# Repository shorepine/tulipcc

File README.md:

# Tulip Creative Computer and AMYboard - portable programmable devices for music, graphics, code and writing

Welcome to the Tulip Creative Computer (Tulip CC) and AMYboard!
 
Tulip is a low power and affordable self-contained portable computer, with a touchscreen display and sound. It's fully programmable - you write code to define your music, games or anything else you can think of. It boots instantaneously into a Python prompt with a lot of built in support for music synthesis, fast graphics and text, hardware MIDI, network access and external sensors. Dive right into making something without distractions or complications. 

The entire system is dedicated to your code, the display and sound, running in real time, on specialized hardware. The hardware and software are fully open source and anyone can [buy one](https://tulip.computer/) or [build one](docs/tulip_build.md). You can use Tulip to make music, code, art, games, or just write. 

[AMYboard](https://amyboard.com) is a headless (no screen) version of Tulip with more audio capability - audio input, modular 10hp and 10vpp audio, S/PDIF digital audio, CV jacks, SD card. It's based on the Tulip code but focused on music synthesis. 

You can now even [run Tulip on the web](https://tulip.computer/run) and [AMYboard on the web](https://amyboard.com/editor) and share your creations with anyone!

Tulip and AMYboard are powered by [MicroPython](https://micropython.org), [AMY](https://github.com/shorepine/amy), and [LVGL](https://lvgl.io). The Tulip hardware runs on the ESP32-S3 chip using the [ESP-IDF](https://github.com/espressif/esp-idf).

 * [**Get a Tulip** from our friends at Makerfabs for only US$59](https://tulip.computer)
 * [**Get an AMYboard** from our friends at Makerfabs for only $29.90](https://amyboard.com)
 * [Just got a Tulip CC? **Check out our getting started guide!**](docs/getting_started.md)
 * [Just got an AMYboard? **Check out our getting started guide!**](docs/amyboard/README.md)
 * [Want to make music with your Tulip? **See our music tutorial**](docs/music.md)
 * [See the full **Tulip API**](docs/tulip_api.md)
 * [**Try out Tulip on the web!**](https://tulip.computer/run/)

 [ **Chat about Tulip on our Discord!**](https://discord.gg/TzBFkUb8pG)

**Check out this video!**

[![Tulip, a musical computer based on Micropython
](https://i.ytimg.com/vi/1lYFjQp7Xrw/maxresdefault.jpg)](https://www.youtube.com/watch?v=1lYFjQp7Xrw "Tulip, a musical computer based on Micropython")

You can use Tulip one of three ways:
 * Tulip is available both as an [off the shelf or DIY hardware project (Tulip CC)](https://tulip.computer/)
 * [Tulip runs on the web](https://tulip.computer/run) with (almost) all the same features. 
 * Tulip can also run as a native app for Mac or Linux (or WSL in Windows) as [Tulip Desktop](docs/tulip_desktop.md)

If you're nervous about getting or building the hardware, [try it out on the web!](https://tulip.computer/run)

The hardware Tulip CC supports:

- 8.5MB of RAM - 2MB is available to MicroPython, and 1.5MB is available for OS memory. The rest is used for the graphics framebuffers (which you can use as storage) and the firmware cache. 
- 32MB flash storage, as a filesystem accesible in Python (24MB left over after OS in ROM)
- An [AMY](https://github.com/shorepine/amy) stereo 120-voice synthesizer engine running locally, or as a wireless controller for an [Alles](https://github.com/shorepine/alles) mesh. Tulip's synth supports additive and subtractive oscillators, an excellent FM synthesis engine, samplers, karplus-strong, high quality analog style filters, a sequencer, and much more. We ship Tulip with a drum machine, voices / patch app, and Juno-6 editor.
- Text frame buffer layer, 128 x 50, with ANSI support for 256 colors, inverse, bold, underline, background color
- Up to 32 sprites on screen, drawn per scanline, with collision detection, from a total of 32KB of bitmap memory (1 byte per pixel)
- A 1024 (+128 overscan) by 600 (+100 overscan) background frame buffer to draw arbitrary bitmaps to, or use as RAM, and which can scroll horizontally / vertically
- WiFi, access http via Python requests or TCP / UDP sockets 
- Adjustable display clock and resolution, defaults to 30 FPS at 1024x600.
- 256 colors
- Can load PNGs from disk to set sprites or background, or generate bitmap data from code
- Built in code and text editor
- Built in BBS chat room and file transfer area called **TULIP ~ WORLD**
- USB keyboard, MIDI and mouse support, including hubs 
- Capactive multi-touch support (mouse on Tulip Desktop and Tulip Web)
- MIDI input and output
- I2C / Grove / Mabee connector, compatible with [many I2C devices like joysticks, keyboard, GPIO, DACs, ADCs, hubs](docs/tulip_api.md#i2c--grove--mabee)
- 575mA power usage @ 5V including display, at medium display brightness, can last for hours on LiPo, 18650s, or USB battery pack 

I've been working on Tulip on and off for years over many hardware iterations and hope that someone out there finds it as fun as I have, either making things with Tulip or working on Tulip itself. I'd love feedback, your own Tulip experiments or pull requests to improve the system.

 * [**Any issues with your Tulip CC? Here's our troubleshooting guide**](docs/troubleshooting.md)
 * [**Learn about our roadmap and find out what we're working on next**](https://github.com/orgs/shorepine/projects/1)
 * [**Build your own Tulip**](docs/tulip_build.md)
 * **[You can read more about the "why" or "how" of Tulip on my website!](https://notes.variogram.com/2024/07/30/tulip-available/)** 

## T-Deck Tulip CC

A **new** small option: get yourself a [T-Deck](https://www.aliexpress.us/item/3256805505920840.html?gatewayAdapt=glo2usa4itemAdapt) and install Tulip CC on it directly! [Check out our T-Deck page for more detail.](tulip/tdeck/README.md)

## Getting started

Once you've [bought a Tulip](https://tulip.computer), [opened Tulip Web](https://tulip.computer/run), [built a Tulip](docs/tulip_build.md) or [installed Tulip Desktop](docs/tulip_desktop.md), you'll see that Tulip boots right into a Python prompt and all interaction with the system happens there. You can make your own Python programs with Tulip's built in editor and execute them, or just experiment on the Tulip REPL prompt in real time.

[**See the full Tulip API**](docs/tulip_api.md) for more details on all the graphics, sound and input functions.

Below are a few getting started tips and small examples. The [full API](docs/tulip_api.md) page has more detail on everything you can do on a Tulip. [**See a more complete getting started page**](docs/getting_started.md) or [**a music making tutorial**](docs/music.md) as well!

```python
# Run a saved Python file. Control-C stops it
cd('ex') # The ex folder has a few examples and graphics in it
execfile("parallax.py")
# If you want to run a Tulip package (folder with other files in it)
run("game")
```

### The Tulip Editor

Tulip ships with a text editor, based on pico/nano. It supports syntax highlighting, search, save/save-as. 

```python
# Opens the Tulip editor to the given filename. 
edit("game.py")
```

### Input and user interface

Tulip supports USB keyboard and mice input as well as touch input. (On Tulip Desktop and Web, mouse clicks act as touch points.) It also comes with UI elements like buttons and sliders to use in your applications, and a way to run mulitple applications as once using callbacks. More in the [full API](docs/tulip_api.md).

```python
(x0, y0, x1, y1, x2, y2) = tulip.touch()
```

### Network

Tulip CC has the capability to connect to a Wi-Fi network, and Python's native requests library will work to access TCP and UDP. We ship a few convenience functions to grab data from URLs as well. More in the [full API](docs/tulip_api.md).

```python
# Join a wifi network (not needed on Tulip Desktop or Web)
tulip.wifi("ssid", "password")

# Get IP address or check if connected
ip_address = tulip.ip() # returns None if not connected

# Save the contents of a URL to disk (needs wifi)
bytes_read = tulip.url_save("https://url", "filename.ext")
```

### Music / sound

Tulip comes with the AMY synthesizer, a very full featured 120-oscillator synth that supports FM, PCM, additive synthesis, partial synthesis, filters, and much more. We also provide a useful "music computer" for scales, chords and progressions. More in the [full API](docs/tulip_api.md) and in the [music tutorial.](docs/music.md) Tulip's version of AMY comes with stereo sound, which you can set per oscillator with the `pan` parameter.

```python
amy.drums() # plays a test song
amy.send(volume=4) # change volume
amy.reset() # stops all music / sounds playing
```
https://user-images.githubusercontent.com/76612/215893940-658144b7-0c6f-42e2-9836-bd271597aab3.mov

### MIDI

Tulip supports MIDI in and out to connect to external music hardware. You can set up a Python callback to respond immediately to any incoming MIDI message. You can also send messages out to MIDI out. More in the [full API](docs/tulip_api.md) and [music tutorial](docs/music.md).

```python
m = tulip.midi_in() # returns bytes of the last MIDI message received
tulip.midi_out((144,60,127)) # sends a note on message
tulip.midi_out(bytes) # Can send bytes or list
```

### Graphics system

The Tulip GPU supports a scrolling background layer, hardware sprites, and a text layer. Much more in the [full API](docs/tulip_api.md).

```python
# Set or get a pixel on the BG
pal_idx = tulip.bg_pixel(x,y)

# Set the contents of a PNG file on the background.
tulip.bg_png(png_filename, x, y)

tulip.bg_scroll(line, x_offset, y_offset, x_speed, y_speed)
```

https://user-images.githubusercontent.com/76612/215895305-7b02ad27-b02a-429a-92ef-f13136e9f9d2.mov

Hardware sprites are supported. They draw over the background and text layer per scanline per frame:

```python
(w, h, bytes) = tulip.sprite_png("filename.png", mem_pos)

...

# Set a sprite x and y position
tulip.sprite_move(12, x, y)
```

https://user-images.githubusercontent.com/76612/215896311-fc0823aa-44bc-4305-85db-a6773db11a98.mov

### Tulip World

Still very much early days, but Tulip supports a native chat and file sharing BBS called **TULIP ~ WORLD** where you can hang out with other Tulip owners. You're able to pull down the latest messages and files and send messages and files yourself. More in the [full API](docs/tulip_api.md).

```python
import world
world.post_message("hello!!") # Sends a message to Tulip World. username required. will prompt if not set
world.upload(filename) # Uploads a file to Tulip World. username required
world.ls() # lists most recent unique filenames/usernames
```

## How to build, compile and help develop Tulip

 * [Get a Tulip!](https://tulip.computer)
 * [Build your own Tulip Creative Computer](docs/tulip_build.md) with FOUR different options.
 * [How to compile and flash Tulip hardware](docs/tulip_flashing.md)
 * [How to run or compile Tulip Desktop](docs/tulip_desktop.md)
 * [The full Tulip API](docs/tulip_api.md)
 * [File any code issues or pull requests!](https://github.com/shorepine/tulipcc/issues)

[ **Chat about Tulip on our Discord!**](https://discord.gg/TzBFkUb8pG)

Two important development guidelines if you'd like to help contribute!

 * Be nice and helpful and don't be afraid to ask questions! We're all doing this for fun and to learn. 
 * Any change or feature must be equivalent across Tulip Desktop and Tulip CC. There are of course limited exceptions to this rule, but please test on hardware before proposing a new feature / change. 

Have fun!

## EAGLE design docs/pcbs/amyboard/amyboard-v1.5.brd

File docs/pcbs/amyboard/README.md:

# AMYboard Schematics

## Revisions

- **v1.5** (`amyboard-v1.5.sch` / `.brd`, from Makerfabs) — same CV/audio circuits as
  v1.4; the negative-rail regulator changed to an SGM2209-ADJ (still -12V). Note the
  GP8413 DACs on the v1.5 production run are a newer date-code batch that powers up in
  a half-scale output range — see the
  [CV troubleshooting entry](../../amyboard/troubleshooting.md#cv-out-voltages-are-wrong-v15-boards).
- **v1.4** — first production revision (`amyboard-v1.4.sch` / `.brd`, PNG above).
- **v1.0 / v1.1dpwe** — prototypes.

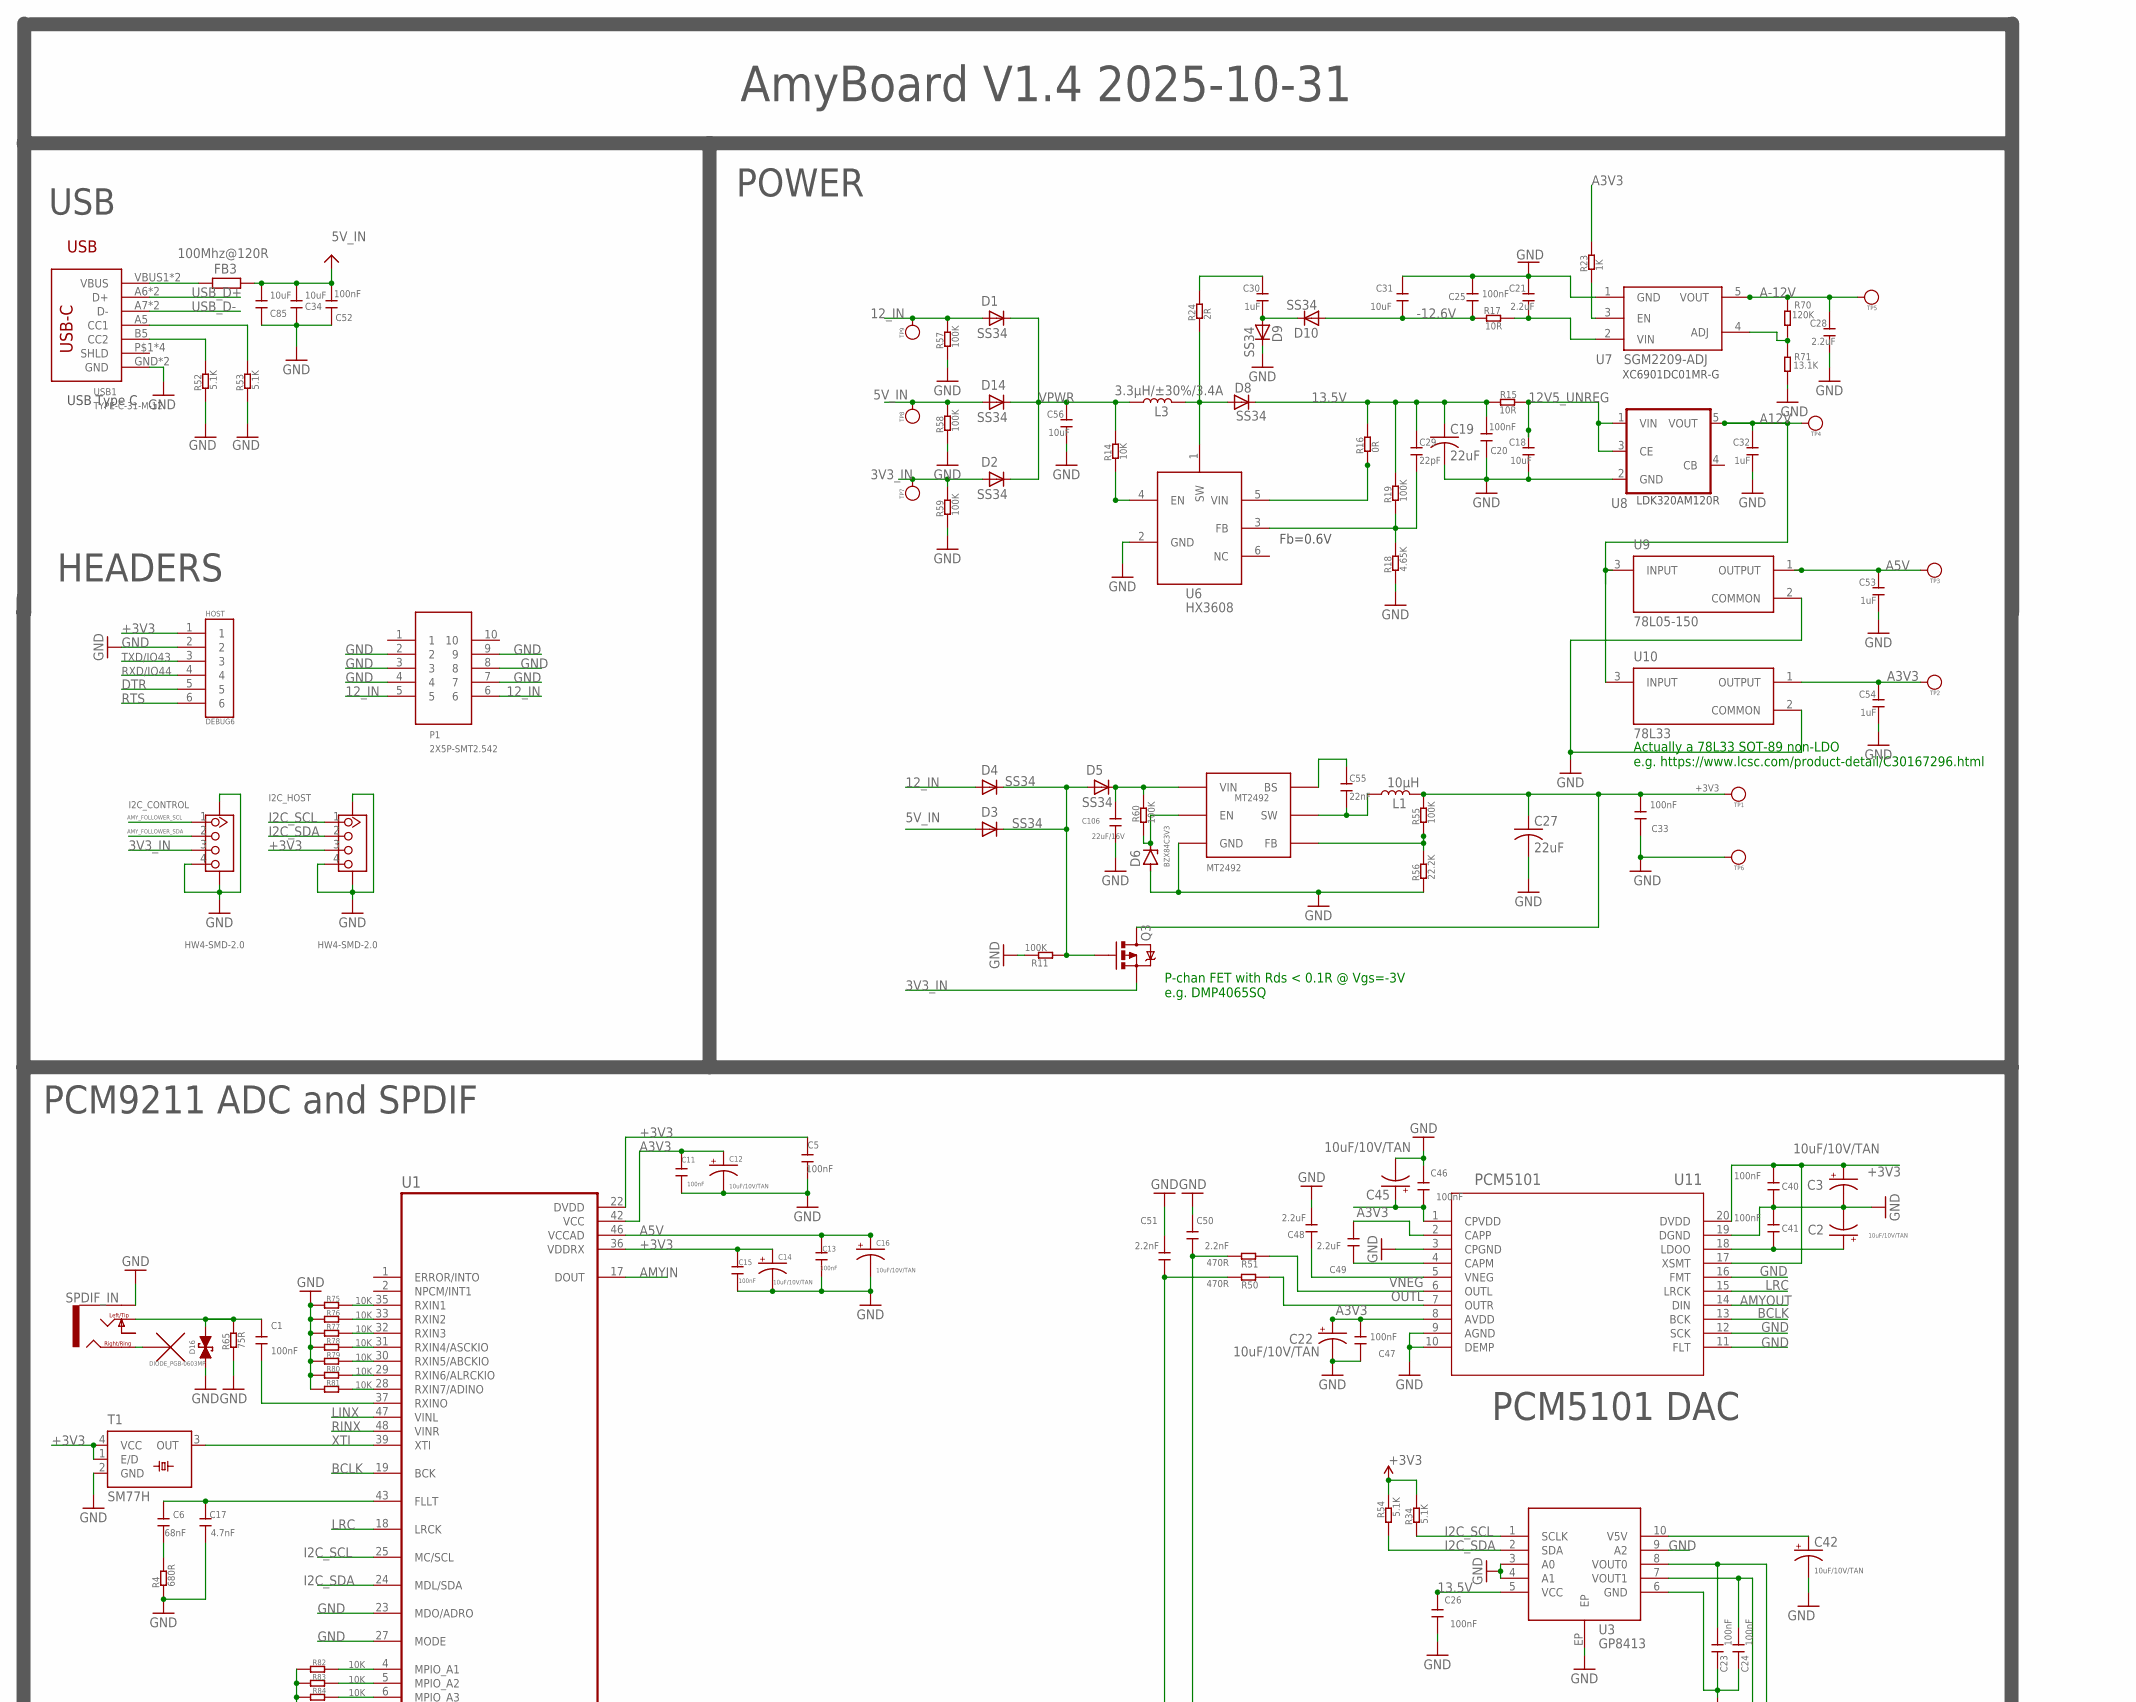
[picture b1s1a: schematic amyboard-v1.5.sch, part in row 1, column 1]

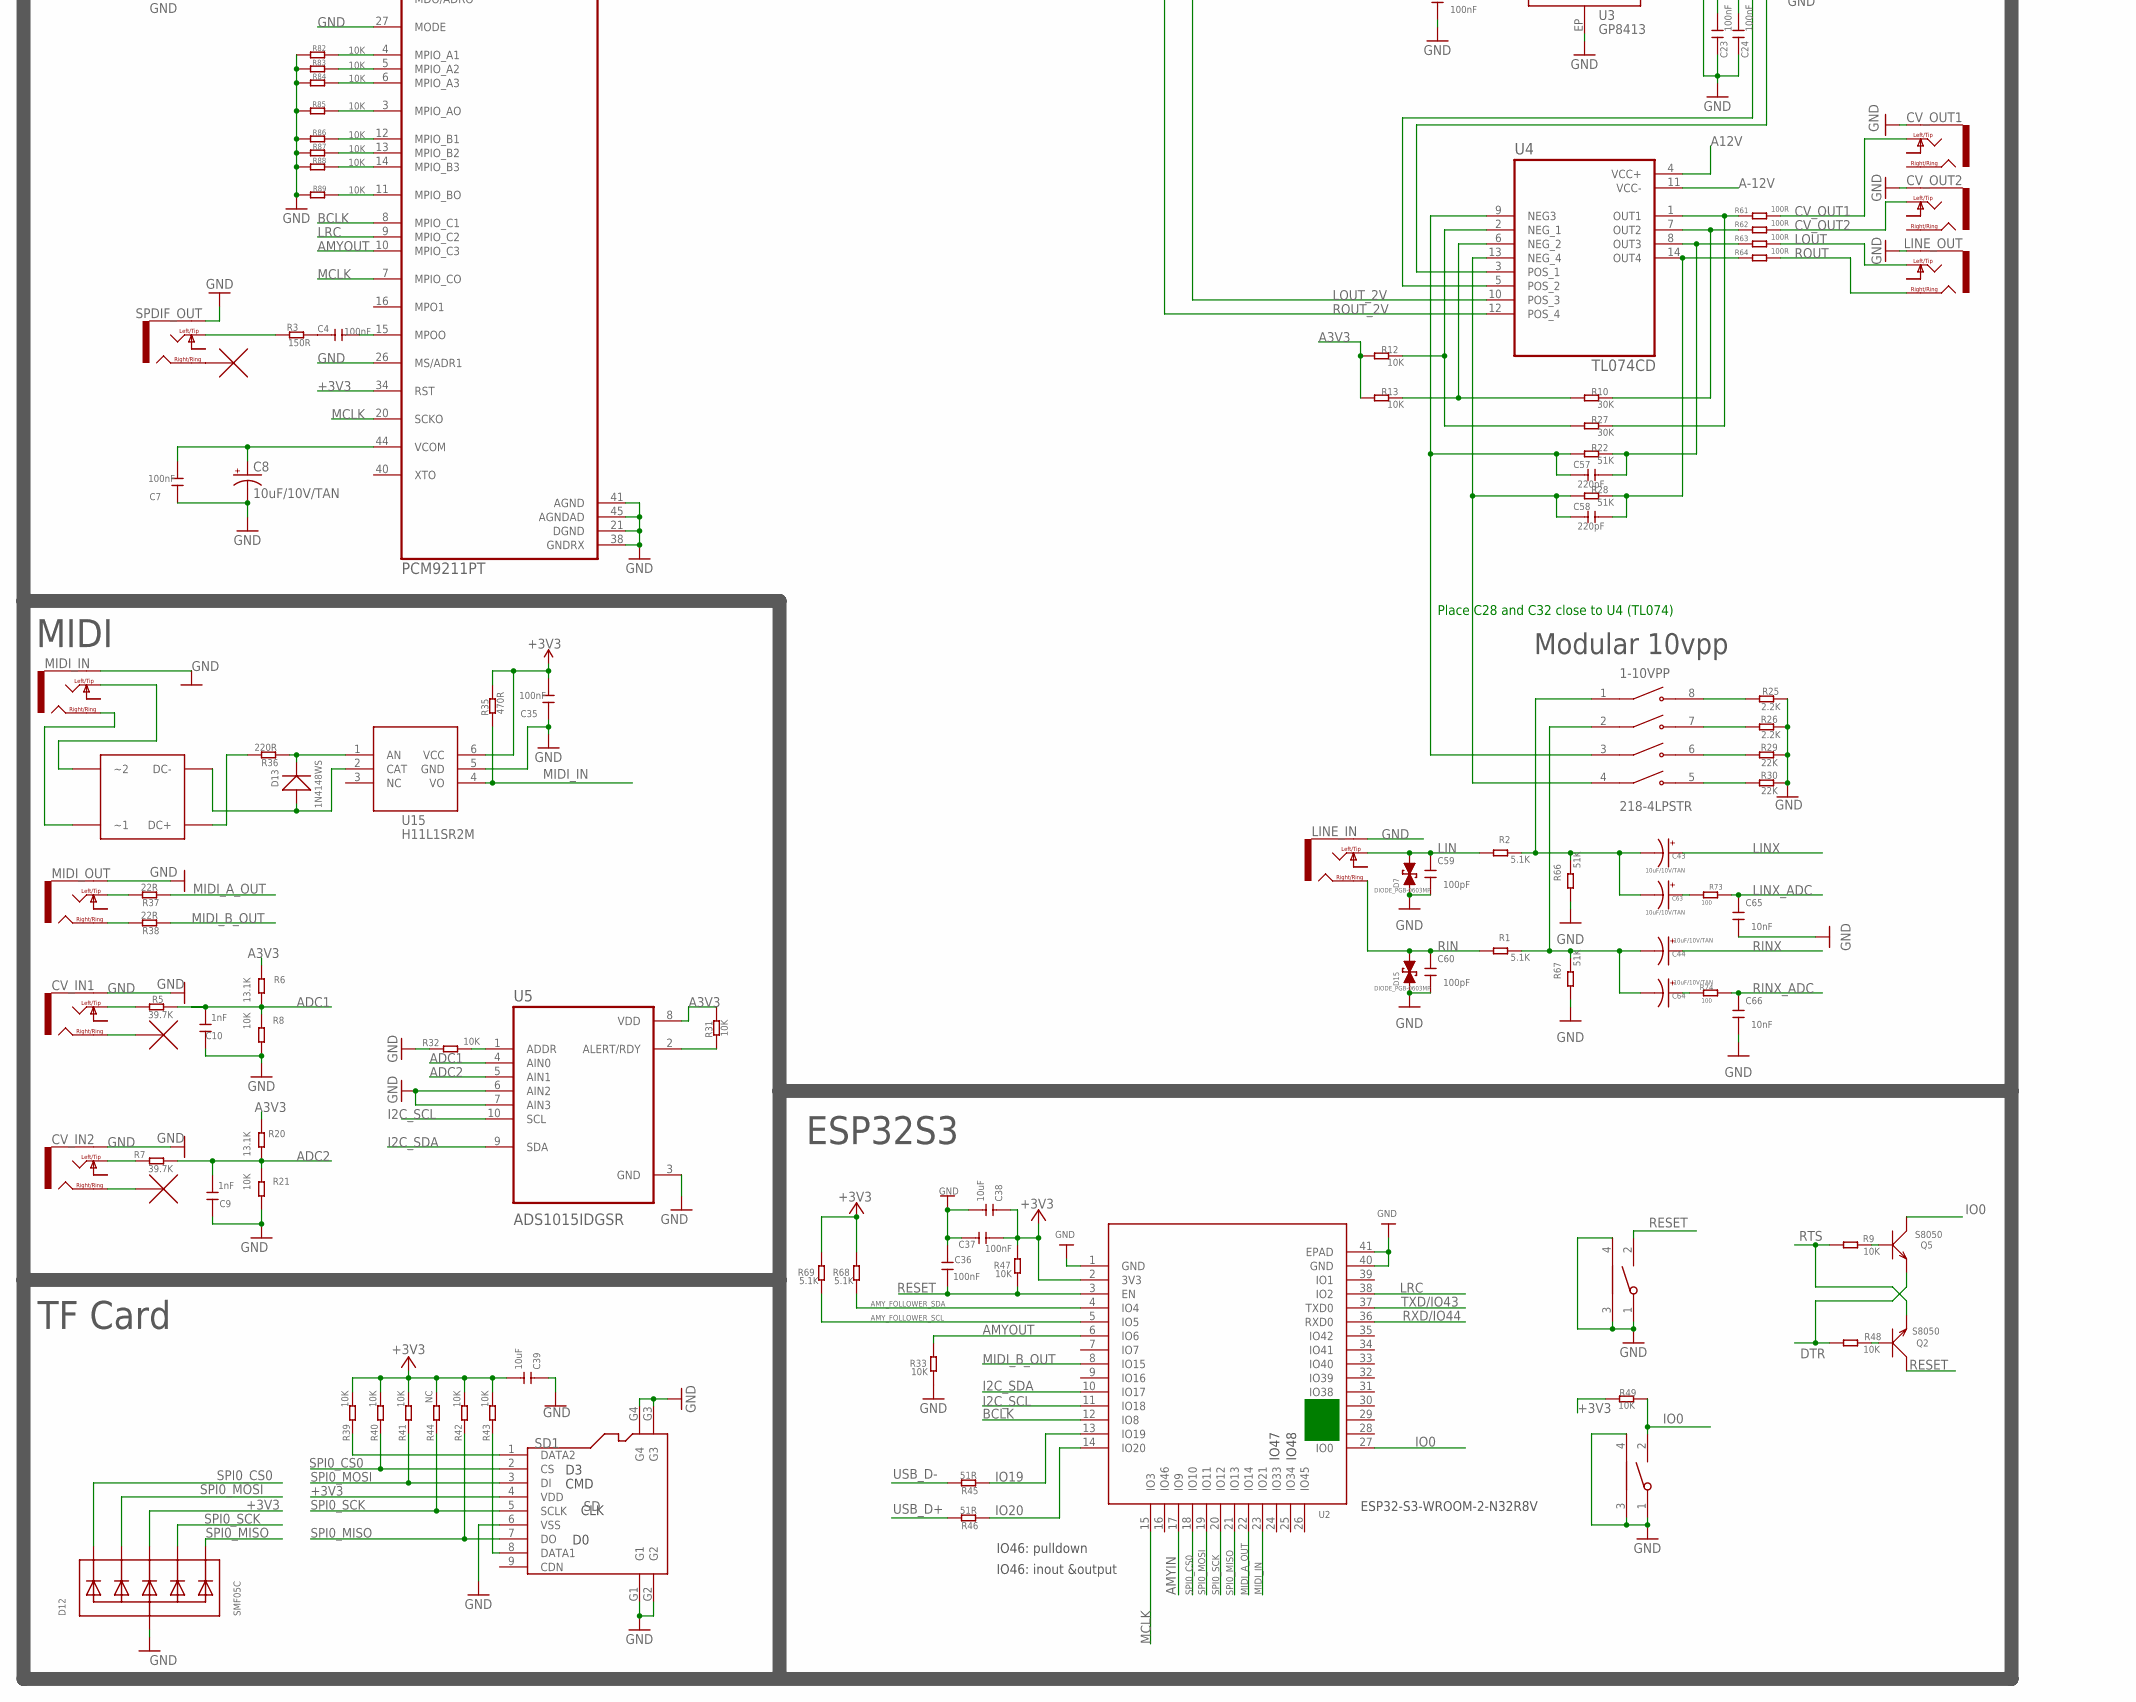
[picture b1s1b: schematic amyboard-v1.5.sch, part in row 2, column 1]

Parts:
1-10VPP: 218-4LPSTR; SW_218-4LPSTR
BOOT: TS24CA; 2*4*3.5MM
C1, C4, C5, C7, C11, C13, C15, C20, C23, C24, C25, C26, C33, C35, C36, C37, C40, C41, C46, C47, C52: 100nF; DISCRETE_C0402
C2, C3, C8, C12, C14, C16, C22, C42, C43, C44, C45, C63, C64: 10uF/10V/TAN; SMC_Z
C6: 68nF; DISCRETE_C0402
C9, C10: 1nF; DISCRETE_C0402
C17: 4.7nF; DISCRETE_C0402
C18, C31, C56: 10uF; C0603
C19, C27: 22uF; C1206
C21, C28: 2.2uF; C0603
C29: 22pF; C0603
C30, C32, C53, C54: 1uF; C0603
C34, C38, C39, C85: 10uF; DISCRETE_C0603
C48, C49: 2.2uF; DISCRETE_C0402
C50, C51: 2.2nF; DISCRETE_C0402
C55: 22nF; C0603
C57, C58: 220pF; DISCRETE_C0402
C59, C60: 100pF; DISCRETE_C0402
C65, C66: 10nF; DISCRETE_C0402
C106: 22uF/16V; 0603
CV_IN1, CV_IN2: NV-PJ3410_STEREO; NV-PJ3410_SOCKET
CV_OUT1, CV_OUT2: NV-PJ3410_STEREO; NV-PJ3410_SOCKET
D1, D2, D3, D4, D5, D8, D9, D10, D14: SS34; DO-214AC
D6: BZX84C3V3; TO236
D7, D15, D16: DIODE_PGB-0603MP
D12: SMF05C; SOT363
D13: 1N4148WS; SOD323
FB3: 100Mhz@120R; R0805
HOST: DEBUG6; DEBUG*6
I2C_CONTROL, I2C_HOST: HW4-SMD-2.0; HW4-SMD-2.0-90D
L1: 10µH; CR54
L3: 3.3µH/±30%/3.4A; CR54
LINE_IN: NV-PJ3410_STEREO; NV-PJ3410_SOCKET
LINE_OUT: NV-PJ3410_STEREO; NV-PJ3410_SOCKET
MB14F: MB14F; MBF
MIDI_IN: NV-PJ3410_STEREO; NV-PJ3410_SOCKET
MIDI_OUT: NV-PJ3410_STEREO; NV-PJ3410_SOCKET
P1: 2X5P-SMT2.542; 2*5P-SMT2.54-HORN
PCM5101: U11; PW20_TEX
Q2, Q5: S8050; SOT23
Q3: DMP4065SQ; SOT23-3
R1, R2, R34, R52, R53, R54, R68, R69: 5.1K; DISCRETE_R0402
R3: 150R; DISCRETE_R0402
R4: 680R; DISCRETE_R0402
R5, R7: 39.7K; DISCRETE_R0402
R6, R20, R71: 13.1K; DISCRETE_R0402
R8, R9, R12, R13, R14, R21, R31, R32, R33, R39, R40, R41, R42, R43, R47, R48, R49, R75, R76, R77, R78, R79, R80, R81, R82, R83, R84, R85, R86, R87, R88, R89: 10K; DISCRETE_R0402
R10, R27: 30K; DISCRETE_R0402
R11, R19, R55, R57, R58, R59, R60: 100K; DISCRETE_R0402
R15: 10R; R0603
R16: 0R; DISCRETE_R0402
R17: 10R; DISCRETE_R0402
R18: 4.65K; DISCRETE_R0402
R22, R28, R66, R67: 51K; DISCRETE_R0402
R23: 1K; DISCRETE_R0402
R24: 2R; DISCRETE_R0402
R25, R26: 2.2K; DISCRETE_R0402
R29, R30: 22K; DISCRETE_R0402
R35, R50, R51: 470R; DISCRETE_R0402
R36: 220R; DISCRETE_R0402
R37, R38: 22R; DISCRETE_R0402
R44: NC; DISCRETE_R0402
R45, R46: 51R; DISCRETE_R0402
R56: 22.2K; DISCRETE_R0402
R61, R62, R63, R64: 100R; DISCRETE_R0402
R65: 75R; DISCRETE_R0402
R70: 120K; DISCRETE_R0402
R73, R74: 100; DISCRETE_R0402
RST: TS24CA; 2*4*3.5MM
SD1: SD; 9P-SMD-W/-RING
SPDIF_IN: NV-PJ3410_STEREO; NV-PJ3410_SOCKET
SPDIF_OUT: NV-PJ3410_STEREO; NV-PJ3410_SOCKET
T1: SM77H
TP1, TP2, TP3, TP4, TP5, TP6, TP7, TP8, TP9: PAD-TEST-POINT-CIRCLE'3535'; TP_3535; PARTNO DNP
U1: PCM9211PT; QFP50P900X900X160-48N
U2: ESP32­S2­SOLO; ESP32-­S2-­SOLO
U3: GP8413; ESOP-10-EP-150MIL
U4: TL074CD; SOIC127P600X175-14N
U5: ADS1015IDGSR; SOP50P490X110-10N
U6: HX3608; SOT-23-6
U7: SGM2209-ADJ; SOT-25
U8: TS5205; SOT25
U9: 78L05-150; VREG_UA78L05ACPKG4
U10: 78L33; VREG_UA78L05ACPKG4
U12: MT2492; SOT23-6
U15: H11L1SR2M; SOP-6-2.54MM
USB1: TYPE-C-31-M-12

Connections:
3V3_IN: D2.A, I2C_CONTROL.3, Q3.2 (S), R59.1, TP7.T
5V_IN: C34.2, C52.2, C85.2, D3.A, D14.A, FB3.2, R58.1, TP8.T
12V5_UNREG: C18.1, R15.1, U8.1 (VIN), U8.3 (CE)
12_IN: D1.A, D4.A, P1.5, P1.6, R57.1, TP9.T
13.5V: C19.1, C20.2, C26.2, C29.1, D8.C, R15.2, R16.1, R19.1, U3.5 (VCC)
+3V3: C3.+, C5.1, C14.+, C15.1, C27.1, C33.2, C35.1, C37.2, C38.1, C39.2, C40.1, D12.4 (C3), HOST.1, I2C_HOST.3, L1.P$2 (2), PCM5101.17 (XSMT), PCM5101.20 (DVDD), Q3.3 (D), R34.1, R35.1, R39.2, R40.2, R41.2, R42.2, R43.2, R44.2, R47.2, R49.2, R54.1, R55.1, R68.2, R69.2, SD1.4 (VDD), T1.1 (E/D), T1.4 (VCC), TP1.T, U1.22 (DVDD), U1.34 (RST), U1.36 (VDDRX), U2.2 (3V3), U15.6 (VCC)
-12.6V: C25.1, C31.2, D10.A, R17.2
A3V3: C11.1, C12.+, C22.+, C45.+, C46.1, C47.1, C54.1, PCM5101.1 (CPVDD), PCM5101.8 (AVDD), R6.2, R12.2, R13.2, R20.2, R23.1, R31.1, TP2.T, U1.42 (VCC), U5.8 (VDD), U10.1 (OUTPUT)
A5V: C13.1, C16.+, C53.1, TP3.T, U1.46 (VCCAD), U9.1 (OUTPUT)
A12V: C32.1, TP4.T, U4.4 (VCC+), U8.5 (VOUT), U9.3 (INPUT), U10.3 (INPUT)
A-12V: C28.1, R70.1, TP5.T, U4.11 (VCC-), U7.5 (VOUT)
ADC1: C10.1, R5.1, R6.1, R8.2, U5.4 (AIN0)
ADC2: C9.1, R7.1, R20.1, R21.2, U5.5 (AIN1)
AMYIN: U1.17 (DOUT), U2.17 (IO9)
AMYOUT: PCM5101.14 (DIN), R33.2, U1.10 (MPIO_C3), U2.6 (IO6)
AMY_FOLLOWER_SCL: I2C_CONTROL.1, R69.1, U2.5 (IO5)
AMY_FOLLOWER_SDA: I2C_CONTROL.2, R68.1, U2.4 (IO4)
BCLK: PCM5101.13 (BCK), U1.8 (MPIO_C1), U1.19 (BCK), U2.12 (IO8)
CV_OUT1: CV_OUT1.LEFT/TIP (TIP), R61.1
CV_OUT2: CV_OUT2.LEFT/TIP (TIP), R62.1
DTR: HOST.5, Q5.2 (E), R48.2
ENABLE: R14.2, U6.4 (EN)
GND: BOOT.1, BOOT.3, BOOT.4, C2.-, C3.-, C5.2, C7.2, C8.-, C9.2, C10.2, C11.2, C12.-, C13.2, C14.-, C15.2, C16.-, C17.1, C18.2, C19.2, C20.1, C21.1, C22.-, C23.1, C24.1, C25.2, C26.1, C27.2, C28.2, C31.1, C32.2, C33.1, C34.1, C35.2, C36.1, C37.1, C38.2, C39.1, C40.2, C41.1, C42.-, C45.-, C46.2, C47.2, C48.1, C50.1, C51.1, C52.1, C53.2, C54.2, C56.2, C59.1, C60.1, C65.1, C66.1, C85.1, C106.2, CV_IN1.GND (EARTH), CV_IN2.GND (EARTH), CV_OUT1.GND (EARTH), CV_OUT2.GND (EARTH), D6.A, D7.1, D9.C, D12.2 (A), D15.1, D16.1, HOST.2, I2C_CONTROL.4, I2C_CONTROL.SS1, I2C_CONTROL.SS2, I2C_HOST.4, I2C_HOST.SS1, I2C_HOST.SS2, LINE_IN.GND (EARTH), LINE_OUT.GND (EARTH), MIDI_IN.GND (EARTH), MIDI_OUT.GND (EARTH), P1.2, P1.3, P1.4, P1.7, P1.8, P1.9, PCM5101.3 (CPGND), PCM5101.9 (AGND), PCM5101.10 (DEMP), PCM5101.11 (FLT), PCM5101.12 (SCK), PCM5101.16 (FMT), PCM5101.19 (DGND), R4.2, R8.1, R11.1, R18.2, R21.1, R25.1, R26.1, R29.1, R30.1, R32.1, R33.1, R52.2, R53.2, R56.2, R57.2, R58.2, R59.2, R65.2, R66.2, R67.2, R71.2, R75.2, R76.2, R77.2, R78.2, R79.2, R80.2, R81.2, R82.2, R83.2, R84.2, R85.2, R86.2, R87.2, R88.2, R89.2, RST.1, RST.3, RST.4, SD1.6 (VSS), SD1.G1, SD1.G2, SD1.G3, SD1.G4, SPDIF_IN.GND (EARTH), SPDIF_OUT.GND (EARTH), T1.2 (GND), TP6.T, U1.21 (DGND), U1.23 (MDO/ADRO), U1.26 (MS/ADR1), U1.27 (MODE), U1.38 (GNDRX), U1.41 (AGND), U1.45 (AGNDAD), U2.1 (GND), U2.40 (GND), U2.41 (EPAD), U3.3 (A0), U3.4 (A1), U3.6 (GND), U3.9 (A2), U3.EP, U5.3 (GND), U5.6 (AIN2), U5.7 (AIN3), U6.2 (GND), U7.1 (GND), U8.2 (GND), U9.2 (COMMON), U10.2 (COMMON), U12.2 (GND), U15.5 (GND), USB1.GND, USB1.GND2 (GND)
I2C_SCL: I2C_HOST.1, R34.2, U1.25 (MC/SCL), U2.11 (IO18), U3.1 (SCLK), U5.10 (SCL)
I2C_SDA: I2C_HOST.2, R54.2, U1.24 (MDL/SDA), U2.10 (IO17), U3.2 (SDA), U5.9 (SDA)
IO0: BOOT.2, Q5.3 (C), R49.1, U2.27 (IO0)
IO19: R45.2, U2.13 (IO19)
IO20: R46.2, U2.14 (IO20)
LIN: C59.2, D7.2, LINE_IN.LEFT/TIP (TIP), R2.2
LINX: C43.+, U1.47 (VINL)
LINX_ADC: C65.2, R73.1
LOUT: LINE_OUT.LEFT/TIP (TIP), R63.1
LOUT_2V: C50.2, R51.1, U4.10 (POS_3)
LRC: PCM5101.15 (LRCK), U1.9 (MPIO_C2), U1.18 (LRCK), U2.38 (IO2)
MCLK: U1.7 (MPIO_CO), U1.20 (SCKO), U2.15 (IO3)
MIDI_A_OUT: R37.2, U2.22 (IO14)
MIDI_B_OUT: R38.2, U2.8 (IO15)
MIDI_IN: R35.2, U2.23 (IO21), U15.4 (VO)
unnamed: C1.1, U1.37 (RXINO)
unnamed: C4.2, R3.1
unnamed: C4.1, U1.15 (MPOO)
unnamed: 1-10VPP.1, C43.-, C63.-, R2.1, R66.1
unnamed: 1-10VPP.2, C44.-, C64.-, R1.1, R67.1
unnamed: C7.1, C8.+, U1.44 (VCOM)
unnamed: C6.2, C17.2, U1.43 (FLLT)
unnamed: C6.1, R4.1
unnamed: R70.2, R71.1, U7.4 (ADJ)
unnamed: CV_IN2.LEFT/TIP (TIP), R7.2
unnamed: C21.2, R17.1, U7.2 (VIN)
unnamed: D13.+, MB14F.DCMINUS (DC-), U15.2 (CAT)
unnamed: C23.2, U3.8 (VOUT0), U4.3 (POS_1)
unnamed: CV_IN1.LEFT/TIP (TIP), R5.2
unnamed: C24.2, U3.7 (VOUT1), U4.5 (POS_2)
unnamed: D8.A, L3.P$2 (2), R24.2, U6.1 (SW)
unnamed: C42.+, U3.10 (V5V)
unnamed: D3.C, D4.C, D5.A, Q3.1 (G), R11.2
unnamed: C106.1, D5.C, R60.1, U12.5 (VIN)
unnamed: C55.2, L1.P$1 (1), U12.6 (SW)
unnamed: R10.1, R62.2, U4.7 (OUT2)
unnamed: C30.1, R24.1
unnamed: R16.2, U6.5 (VIN)
unnamed: C30.2, D9.A, D10.C
unnamed: R23.2, U7.3 (EN)
unnamed: R10.2, R13.1, U4.6 (NEG_2)
unnamed: R27.1, R61.2, U4.1 (OUT1)
unnamed: R12.1, R27.2, U4.2 (NEG_1)
unnamed: Q2.1 (B), R48.1
unnamed: 1-10VPP.5, R30.2
unnamed: 1-10VPP.6, R29.2
unnamed: Q5.1 (B), R9.1
unnamed: R53.1, USB1.A5 (CC1)
unnamed: R52.1, USB1.B5 (CC2)
unnamed: 1-10VPP.8, R25.2
unnamed: 1-10VPP.7, R26.2
unnamed: FB3.1, USB1.VBUS1 (VBUS), USB1.VBUS2 (VBUS)
unnamed: R31.2, U5.2 (ALERT/RDY)
unnamed: 1-10VPP.3, C57.1, R22.2, U4.9 (NEG3)
unnamed: 1-10VPP.4, C58.1, R28.2, U4.13 (NEG_4)
unnamed: R32.2, U5.1 (ADDR)
unnamed: R55.2, R56.1, U12.3 (FB)
unnamed: C2.+, C41.2, PCM5101.18 (LDOO)
unnamed: MB14F.DCPLUS (DC+), R36.1
unnamed: PCM5101.7 (OUTR), R50.2
unnamed: C49.2, PCM5101.4 (CAPM)
unnamed: C49.1, PCM5101.2 (CAPP)
unnamed: C55.1, U12.1 (BS)
unnamed: MB14F.AC1 (~1), MIDI_IN.RIGHT/RING (RING)
unnamed: MB14F.AC2 (~2), MIDI_IN.LEFT/TIP (TIP)
unnamed: D6.C, R60.2, U12.4 (EN)
unnamed: D13.-, R36.2, U15.1 (AN)
unnamed: MIDI_OUT.LEFT/TIP (TIP), R37.1
unnamed: MIDI_OUT.RIGHT/RING (RING), R38.1
unnamed: C29.2, R18.1, R19.2, U6.3 (FB)
unnamed: C58.2, R28.1, R64.2, U4.14 (OUT4)
unnamed: C57.2, R22.1, R63.2, U4.8 (OUT3)
unnamed: R75.1, U1.35 (RXIN1)
unnamed: R76.1, U1.33 (RXIN2)
unnamed: C63.+, R73.2
unnamed: C64.+, R74.2
unnamed: R39.1, SD1.1 (DATA2)
unnamed: R77.1, U1.32 (RXIN3)
unnamed: R43.1, SD1.8 (DATA1)
unnamed: R78.1, U1.31 (RXIN4/ASCKIO)
unnamed: R79.1, U1.30 (RXIN5/ABCKIO)
unnamed: R80.1, U1.29 (RXIN6/ALRCKIO)
unnamed: R81.1, U1.28 (RXIN7/ADINO)
unnamed: R82.1, U1.4 (MPIO_A1)
unnamed: R83.1, U1.5 (MPIO_A2)
unnamed: R84.1, U1.6 (MPIO_A3)
unnamed: R85.1, U1.3 (MPIO_AO)
unnamed: R86.1, U1.12 (MPIO_B1)
unnamed: R87.1, U1.13 (MPIO_B2)
unnamed: R88.1, U1.14 (MPIO_B3)
unnamed: R89.1, U1.11 (MPIO_BO)
OUTL: PCM5101.6 (OUTL), R51.2
RESET: C36.2, Q2.3 (C), R47.1, RST.2, U2.3 (EN)
RIN: C60.2, D15.2, LINE_IN.RIGHT/RING (RING), R1.2
RINX: C44.+, U1.48 (VINR)
RINX_ADC: C66.2, R74.1
ROUT: LINE_OUT.RIGHT/RING (RING), R64.1
ROUT_2V: C51.2, R50.1, U4.12 (POS_4)
RTS: HOST.6, Q2.2 (E), R9.2
RXD/IO44: HOST.4, U2.36 (RXD0)
SPDIFIN_SIGNAL: C1.2, D16.2, R65.1, SPDIF_IN.LEFT/TIP (TIP)
SPDIFOUT_SIGNAL: R3.2, SPDIF_OUT.LEFT/TIP (TIP)
SPI0_CS0: D12.1 (C1), R40.1, SD1.2 (CS), U2.18 (IO10)
SPI0_MISO: D12.6 (C5), R42.1, SD1.7 (DO), U2.21 (IO13)
SPI0_MOSI: D12.3 (C2), R41.1, SD1.3 (DI), U2.19 (IO11)
SPI0_SCK: D12.5 (C4), R44.1, SD1.5 (SCLK), U2.20 (IO12)
TXD/IO43: HOST.3, U2.37 (TXD0)
USB_D+: R46.1, USB1.A6 (D+), USB1.B6 (D+)
USB_D-: R45.1, USB1.A7 (D-), USB1.B7 (D-)
VNEG: C48.2, PCM5101.5 (VNEG)
VPWR: C56.1, D1.C, D2.C, D14.C, L3.P$1 (1), R14.1
XTI: T1.3 (OUT), U1.39 (XTI)

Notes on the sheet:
USB
USB Type C
IO46: pulldown
IO46: inout &output
ESP32-S3-WROOM-2-N32R8V
IO47
IO48
MIDI
PCM9211 ADC and SPDIF
ESP32S3
HEADERS
TF Card
CMD
CLK
Modular 10vpp
Fb=0.6V
PCM5101 DAC
Place C28 and C32 close to U4 (TL074)
POWER
AmyBoard V1.4 2025-10-31
P-chan FET with Rds < 0.1R @ Vgs=-3V e.g. DMP4065SQ
LDK320AM120R
XC6901DC01MR-G
Actually a 78L33 SOT-89 non-LDO e.g. https://www.lcsc.com/product-detail/C30167296.html

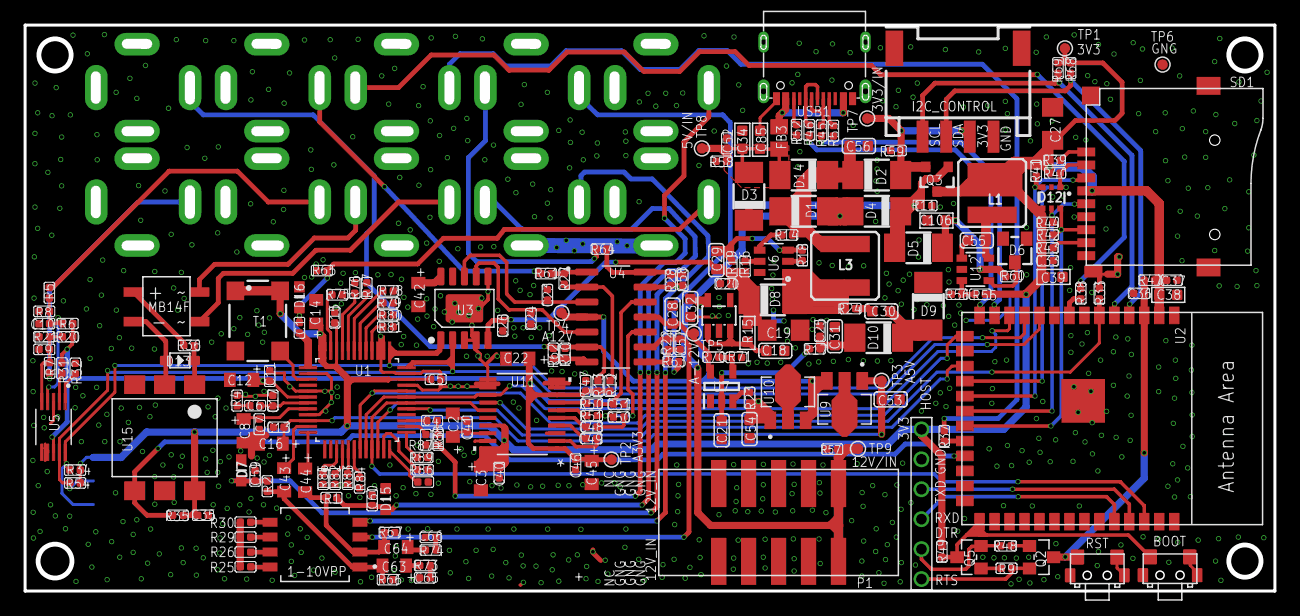
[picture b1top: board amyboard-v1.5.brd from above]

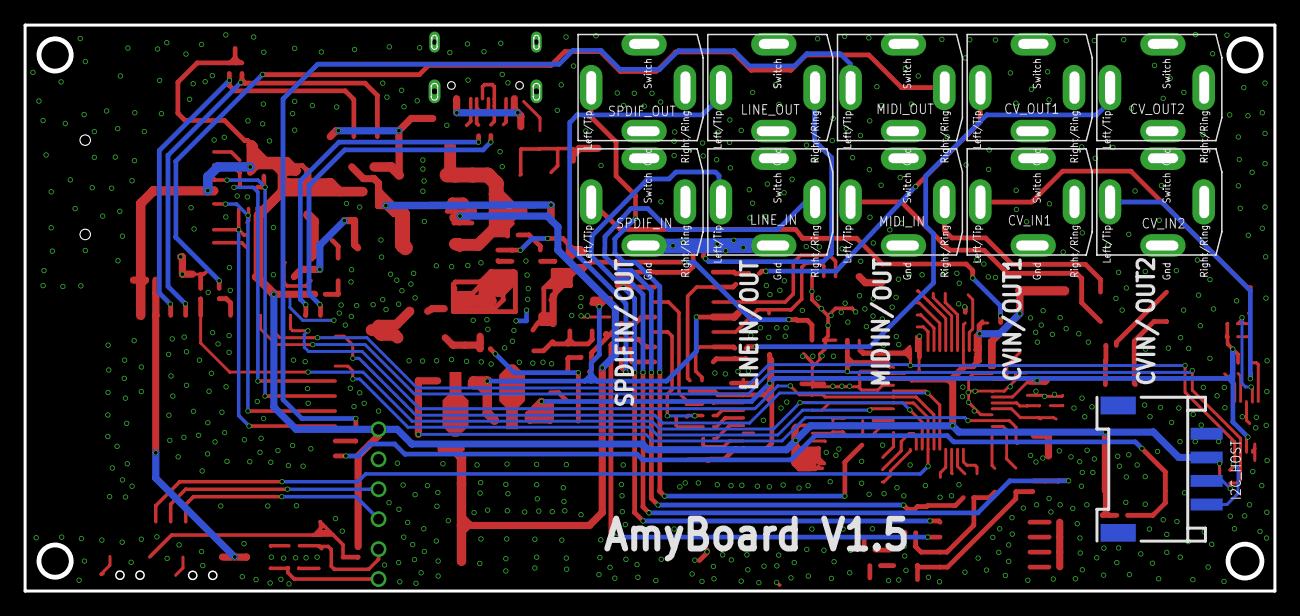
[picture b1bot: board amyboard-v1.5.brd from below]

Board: 2 copper layers, 106.0 x 48.0 mm, 218 parts (11 on the bottom side), 135 nets.

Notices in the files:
parts and their libraries:
microbuilder: This work is placed in the public domain, and may be freely used for commercial and non-commercial work with the following conditions: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
SparkFun-Coils: Licensing: Creative Commons ShareAlike 4.0 International - https://creativecommons.org/licenses/by-sa/4.0
